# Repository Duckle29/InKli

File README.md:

# InKli

From the Danish "Indeklima" or "indoor climate", is an small sensor box, measuring CO2, temperature and relative humidity.

It displays this on an E-paper display, to allow you to keep an eye on the air in the room you're in.  
Additionally, as it is made with ESPHome, it can also easily connect to a Homeassistant instance, for further home automation and logging.

## History
Quite some time ago I built an air quality monitor, and played around with it. (https://blog.mikkel.cc/posts/airq/) It had PM10 sensors, CO2 sensors and BME680 for TVOC.

I've since had this running, and while it was fine, it was bulky, and I only ever really paid attention to the temperature, humidity and CO2 sensors.
The display I used on that box also had issues. Mainly with the backlight being a significant heat source, and an annoyance at night.

So now this is the replacement.
It has:
- ESP32
- 2.13" Waveshare E-paper display  (https://www.waveshare.com/2.13inch-e-paper.htm)
- IR remote demodulator
- 2 side-firing high-current IR LEDs 
- QWIIC port for future expansion / experimentation
- Single push button
- Touch-pad under screen (tested, works so~so, not great)
It also has a (hopefully) quite efficient 3V3 buck regulator to reduce self heating. (pretty good, seems around 2-3C self heating enclosed, mostly from the ESP itself )

At this point, I have the displays and the sensors. I'm getting most things working first, so I don't learn I've used a strapping pin when I have PCBs in hand and they don't cooperate.
I'm pretty happy with the simple display layout, and will see tomorrow how the graph turns out (set to 8h)

The IR blasters are there because one of these sensors will pull double duty, and act as an IR remote for a heat pump. 
On the rest of the PCBs these probably won't be populated.

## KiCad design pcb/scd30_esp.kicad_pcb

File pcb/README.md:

# SCD30 ESP32 backback

This is a small PCB combining an ESP32 WROOM module with an SCD30. It's intended to be USB powered, and has the option to mount a CH340C if you want on-board USB<>serial.

It's intended for use with ESPHome or similar.

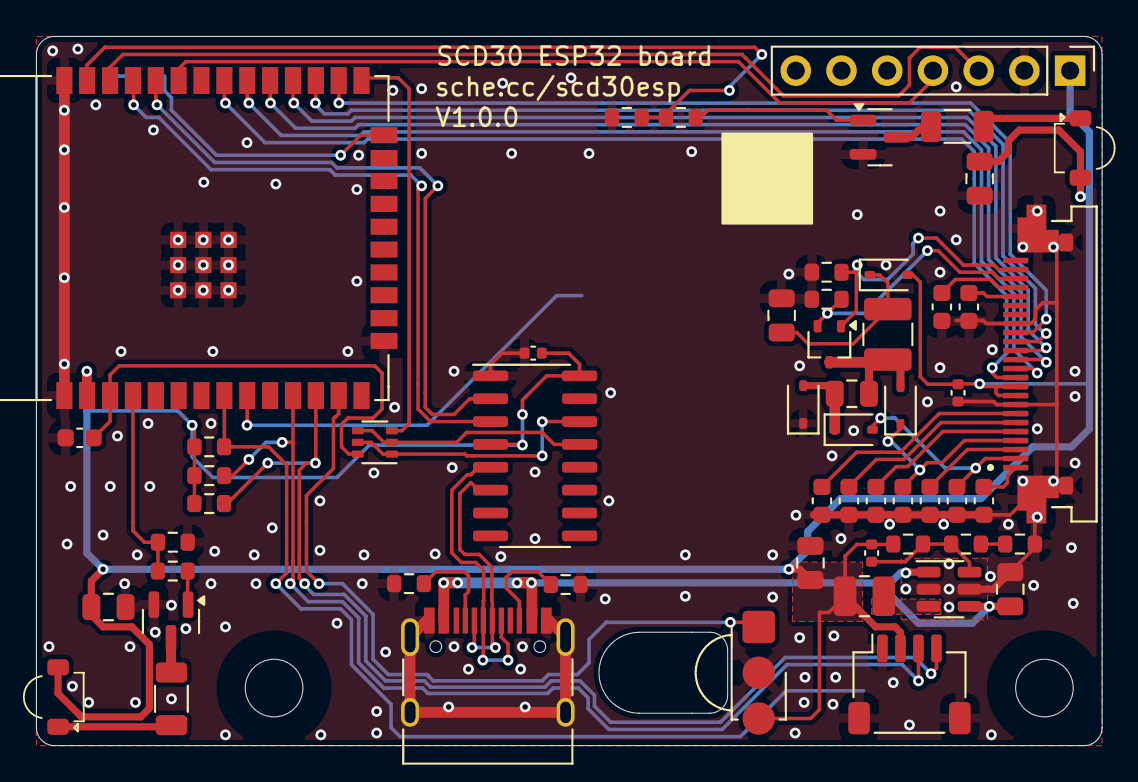
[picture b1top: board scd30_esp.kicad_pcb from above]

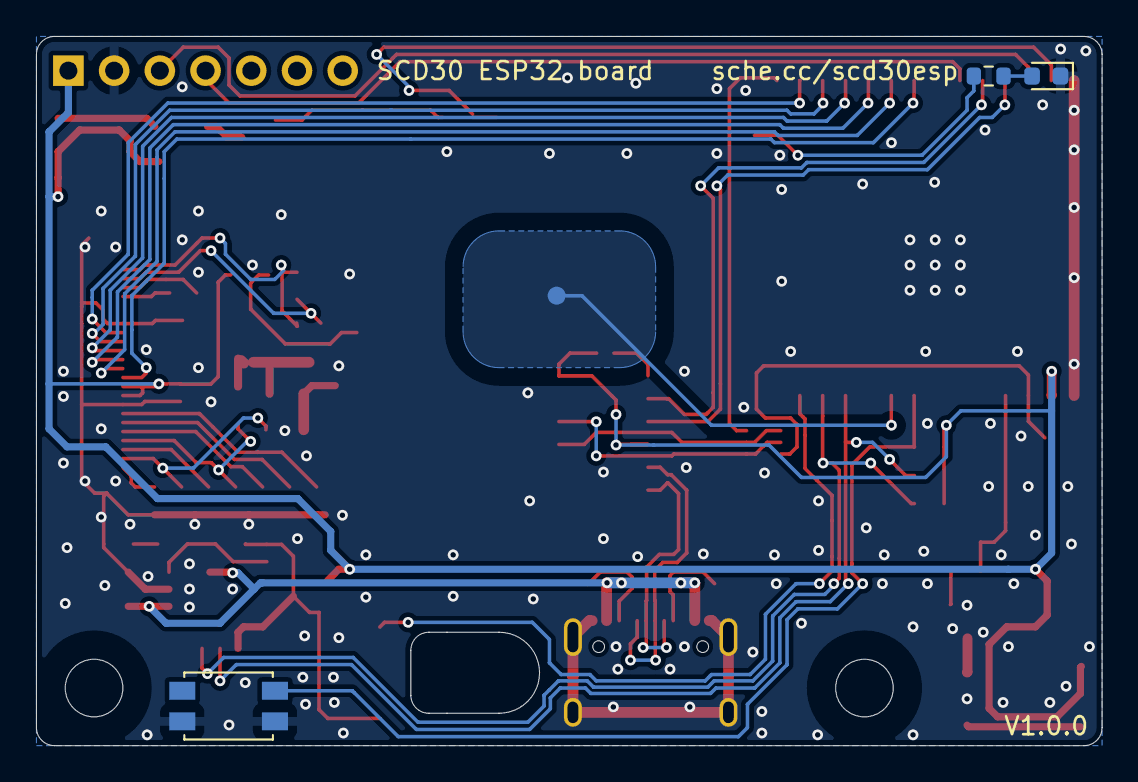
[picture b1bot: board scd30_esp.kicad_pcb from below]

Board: 2 copper layers, 59.2 x 39.4 mm, 59 parts (4 on the bottom side), 53 nets.

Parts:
C1: 120pF; C_0402_1005Metric
C2, C6, C7: 22uF; C_0805_2012Metric
C3: 4.7uF; C_0805_2012Metric
C4, C20: 0.1uF; C_0402_1005Metric
C5, C10, C11, C12, C13, C14, C15, C16, C17, C18: 1uF; C_0603_1608Metric
C8, C9: 4u7; C_0805_2012Metric
D1, D2, D3, D4: NSR0530HT1G; D_SOD-323
D5, D6: LED_Small; LED_Vishay_VSMB2943SL
D7: LED_Small; LED_0603_1608Metric
J1: SCD30; PinHeader_1x07_P2.54mm_Vertical
J2: USB_C_Receptacle_USB2.0; USB_C_Receptacle_HRO_TYPE-C-31-M-12
J3: 24P P0.5mm waveshare E-paper display; AMPHENOL_SFV24R-4STE1HLF
J4: QWIIC; JST_SH_SM04B-SRSS-TB_1x04-1MP_P1.00mm_Horizontal
L1: 1uH; L_1008_2520Metric
L2: 68uF; L_1210_3225Metric
Q1: Si1308EDL; SOT-323_SC-70
Q2, Q4: Q_NMOS_GSD; SOT-23
Q3: BSS138PS; SOT-363_SC-70-6
R1: 82k; R_0603_1608Metric
R2: 360k; R_0603_1608Metric
R3, R7, R10, R13, R14: 10k; R_0603_1608Metric
R4, R5: 5k1; R_0603_1608Metric
R6: 3R; R_0603_1608Metric
R8, R9, R12, R15: 2k2; R_0603_1608Metric
R11, R16: 3R; R_1206_3216Metric
R17: 1k; R_0603_1608Metric
SW1: SW_SPST; SW_SPST_EVQP2
TP1: Touch TP; TestPoint_Pad_D1.0mm
U1: TPS62A01PDDCR; SOT-23-6
U2: ESP32-WROOM-E; ESP32-WROOM-32E
U3: CH340C; SOIC-16_3.9x9.9mm_P1.27mm
U4: TSOP38G36; Vishay_MINICAST-3Pin

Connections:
+3V3: C1.1, C2.1, C4.1, C6.1, C7.1, C20.1, D1.2 (A), D5.2 (A), D6.2 (A), J1.1, J3.9, J3.10, J4.2, L1.2, R1.1, R8.1, R9.1, R10.1, U2.2 (3V3), U3.4 (V3), U3.16 (VCC), U4.3 (Vs)
/BTN: R10.2, SW1.1 (A), U2.8 (32K_XP/GPIO32/ADC1_CH4)
/D+: J2.A6 (D+), J2.B6 (D+), U3.5 (UD+)
/D-: J2.A7 (D-), J2.B7 (D-), U3.6 (UD-)
/DISP_BUSY: J3.16, U2.26 (ADC2_CH0/GPIO4)
/DISP_SDA: J3.11, U2.31 (GPIO19)
/ESP_EN: C5.1, Q3.6 (D), U2.3 (EN/CHIP_PU)
/ESP_IO0: Q3.3 (D), U2.25 (GPIO0/BOOT/ADC2_CH1)
/IR_RX: U2.13 (MTMS/GPIO14/ADC2_CH6), U4.1 (OUT)
/IR_TX_L: R12.1, R13.1, U2.37 (GPIO23)
/IR_TX_R: R14.1, R15.1, U2.4 (SENSOR_VP/GPIO36/ADC1_CH0)
/MCU_RX+: U2.34 (U0RXD/GPIO3), U3.2 (TXD)
/MCU_TX-: U2.35 (U0TXD/GPIO1), U3.3 (RXD)
/QWIIC_SCL: J4.4, R9.2, U2.12 (ADC2_CH7/GPIO27)
/QWIIC_SDA: J4.3, R8.2, U2.11 (DAC_2/ADC2_CH9/GPIO26)
/SCL: J1.3, U2.36 (GPIO22)
/SCLK: J3.12, U2.30 (GPIO18)
/SDA: J1.4, U2.33 (GPIO21)
/TOUCH: TP1.1, U2.9 (32K_XN/GPIO33/ADC1_CH5)
/Waveshare E-ink/GDR: J3.23, Q1.1 (G), R7.1
/Waveshare E-ink/RESE: J3.22, Q1.2 (S), R6.1
/Waveshare E-ink/VCOM: C10.1, J3.1
/Waveshare E-ink/VGH: C13.1, D4.1 (K), J3.4
/Waveshare E-ink/VGL: C11.1, D3.2 (A), J3.2
/Waveshare E-ink/VPP: C15.1, J3.6
/Waveshare E-ink/VSH1: C14.1, J3.5
/Waveshare E-ink/VSH2: C17.1, J3.20
/Waveshare E-ink/VSL: C12.1, J3.3
/Waveshare E-ink/V_CORE: C16.1, J3.7
/status_led: R17.2, U2.24 (ADC2_CH2/GPIO2)
/~DISP_CS: J3.13, U2.29 (GPIO5)
/~DISP_D/C: J3.14, U2.28 (GPIO17)
/~DISP_RST: J3.15, U2.27 (GPIO16)
GND: C2.2, C3.2, C4.2, C5.2, C6.2, C7.2, C9.2, C10.2, C11.2, C12.2, C13.2, C14.2, C15.2, C16.2, C17.2, C18.2, C20.2, D2.1 (K), D7.1 (K), J1.2, J2.A1 (GND), J2.A12 (GND), J2.B1 (GND), J2.B12 (GND), J2.S1 (SHIELD), J3.8, J3.17, J3.MP (MountPin), J4.1, J4.MP (MountPin), Q2.2 (S), Q4.2 (S), R3.2, R4.2, R5.2, R6.2, R7.2, R13.2, R14.2, SW1.2 (B), U1.2 (GND), U1.5 (PG), U2.1 (GND), U2.15 (GND), U2.38 (GND), U2.39 (GND_THERMAL), U3.1 (GND), U4.2 (GND)
unnamed: C9.1, D1.1 (K), L2.1
unnamed: C8.2, D2.2 (A), D3.1 (K)
unnamed: C8.1, D4.2 (A), L2.2, Q1.3 (D)
unnamed: D5.1 (K), R11.1
unnamed: D6.1 (K), R16.1
unnamed: D7.2 (A), R17.1
unnamed: J2.A5 (CC1), R5.1
unnamed: J2.B5 (CC2), R4.1
unnamed: C18.1, J3.21
unnamed: Q2.3 (D), R11.2
unnamed: Q2.1 (G), R12.2
unnamed: Q3.2 (G), Q3.4 (S), U3.13 (~DTR)
unnamed: Q3.1 (S), Q3.5 (G), U3.14 (~RTS)
unnamed: Q4.3 (D), R16.2
unnamed: Q4.1 (G), R15.2
unnamed: R2.2, R3.1
unnamed: C1.2, R1.2, R2.1, U1.6 (FB)
unnamed: L1.1, U1.3 (SW)
VBUS: C3.1, J2.A4 (VBUS), J2.A9 (VBUS), J2.B4 (VBUS), J2.B9 (VBUS), U1.1 (EN), U1.4 (VIN)

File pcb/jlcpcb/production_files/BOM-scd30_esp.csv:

Comment,Designator,Footprint,LCSC,Quantity
120pF,C1,C_0402_1005Metric,C106996,1
0.1uF,"C20,C4",C_0402_1005Metric,C1525,2
1uF,"C10,C11,C12,C13,C14,C15,C16,C17,C5,C8,C9",C_0603_1608Metric,C15849,11
USB_C_Receptacle_USB2.0,J2,USB_C_Receptacle_HRO_TYPE-C-31-M-12,C165948,1
BSS138PS,Q3,SOT-363_SC-70-6,C193381,1
4.7uF,C3,C_0805_2012Metric,C19666,1
68uF,L2,L_1210_3225Metric,C223228,1
TPS62A01PDDCR,U1,SOT-23-6,C22445521,1
LED_Small,D7,LED_0603_1608Metric,C2286,1
360k,R2,R_0603_1608Metric,C23146,1
82k,R1,R_0603_1608Metric,C23254,1
10k,"R10,R13,R14,R17,R3,R7",R_0603_1608Metric,C25804,6
1uH,L1,L_1008_2520Metric,C435392,1
22uF,"C2,C6,C7",C_0805_2012Metric,C45783,3
Si1308EDL,Q1,SOT-323_SC-70,C469327,1
SW_SPST,SW1,SW_SPST_EVQP2,C512395,1
24P P0.5mm waveshare E-paper display,J3,AMPHENOL_SFV24R-4STE1HLF,C5343283,1
NSR0530HT1G,"D1,D2,D3,D4",D_SOD-323,C556393,4
2k2,"R12,R15,R4,R5,R8,R9",R_0603_1608Metric,C6119849,6
ESP32-WROOM-E,U2,ESP32-WROOM-32E,C701342,1
CH340C,U3,SOIC-16_3.9x9.9mm_P1.27mm,C7464026,1
3R,R6,R_0603_1608Metric,,1
TSOP38G36,U4,Vishay_MINICAST-3Pin,,1

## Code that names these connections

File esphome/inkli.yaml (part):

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  - platform: gpio
    id: btn
    pin:
      number: GPIO32
      inverted: True
      #allow_other_uses: True
      mode:
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          - component.update: disp

  # - platform: esp32_touch
  #   pin: GPIO33
  #   threshold: 1040
  #   id: touch_test
  #   filters:
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output:
  - platform: ledc
    id: led_status
    pin: GPIO2
    frequency: 19531

graph:
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display:
  - platform: waveshare_epaper
    id: disp
    cs_pin: GPIO5
    dc_pin: GPIO17
    reset_pin: GPIO16
    busy_pin: GPIO4
    model: 2.13inv3
    full_update_every: 60
    rotation: 270
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    type: char[9]

spi:
  clk_pin: GPIO18
  mosi_pin: GPIO19

i2c:
  - id: i2c_scd30
    sda: GPIO21
    scl: GPIO22
    scan: False
  
  - id: qwiic
    sda: GPIO26
    scl: GPIO27
    scan: True

http_request:
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
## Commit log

2024-12-28 Saved schematic
2025-01-01 Initial schematic
2025-01-03 Initial layout
2025-01-17 moved files to sub-folders
2025-01-17 readme
2025-01-23 Added alternate footprint for XFCN FPC connector
2025-01-23 nudged components, added version text
2025-01-23 Added JLCPCB production files
2025-02-15 Initial esphome yaml, and 3D CAD
2025-02-15 Commented out min_version for now
2025-02-15 Added factory reset
2025-02-15 unbumped version
2025-02-15 Dedupe button
2025-02-16 Updated hosing design. Name change to InKli
2025-02-16 Added setup instructions
2025-02-16 Update case clearances slightly
2025-02-19 Set min ESPHome version to 2025.02.00
2025-02-19 Added actions for CI and publishing
2025-02-19 remove double file extension
2025-02-19 no .factory yaml
2025-02-19 Updated workflow actions to v4
2025-02-19 change publish workflow trigger
2025-03-04 Add wifi info to main screen, and disable wifi if unconnected for >5min
2025-03-29 Added image to readme
2025-04-20 Updated CAD files for better printability
2025-04-20 Don't do CI for now
2025-04-20 use latest esphome for builds
2025-04-20 Trigger workflow on release trigger
2025-04-20 no ci
2025-04-20 Version bump
2025-04-20 Work on http ota
2025-04-21 Version bump to test webhook
2025-04-21 Initial work on pushing files to ota server over SCP
2025-04-21 version bump for test
2025-04-21 fix string, depend on upload job
2025-04-21 Upload files to proper subdir
2025-04-21 Got http ota working
2025-04-21 Remove touch
2025-04-21 Cherrypicked wifi info commit
2025-04-27 Do a display update when triggering a new display page
